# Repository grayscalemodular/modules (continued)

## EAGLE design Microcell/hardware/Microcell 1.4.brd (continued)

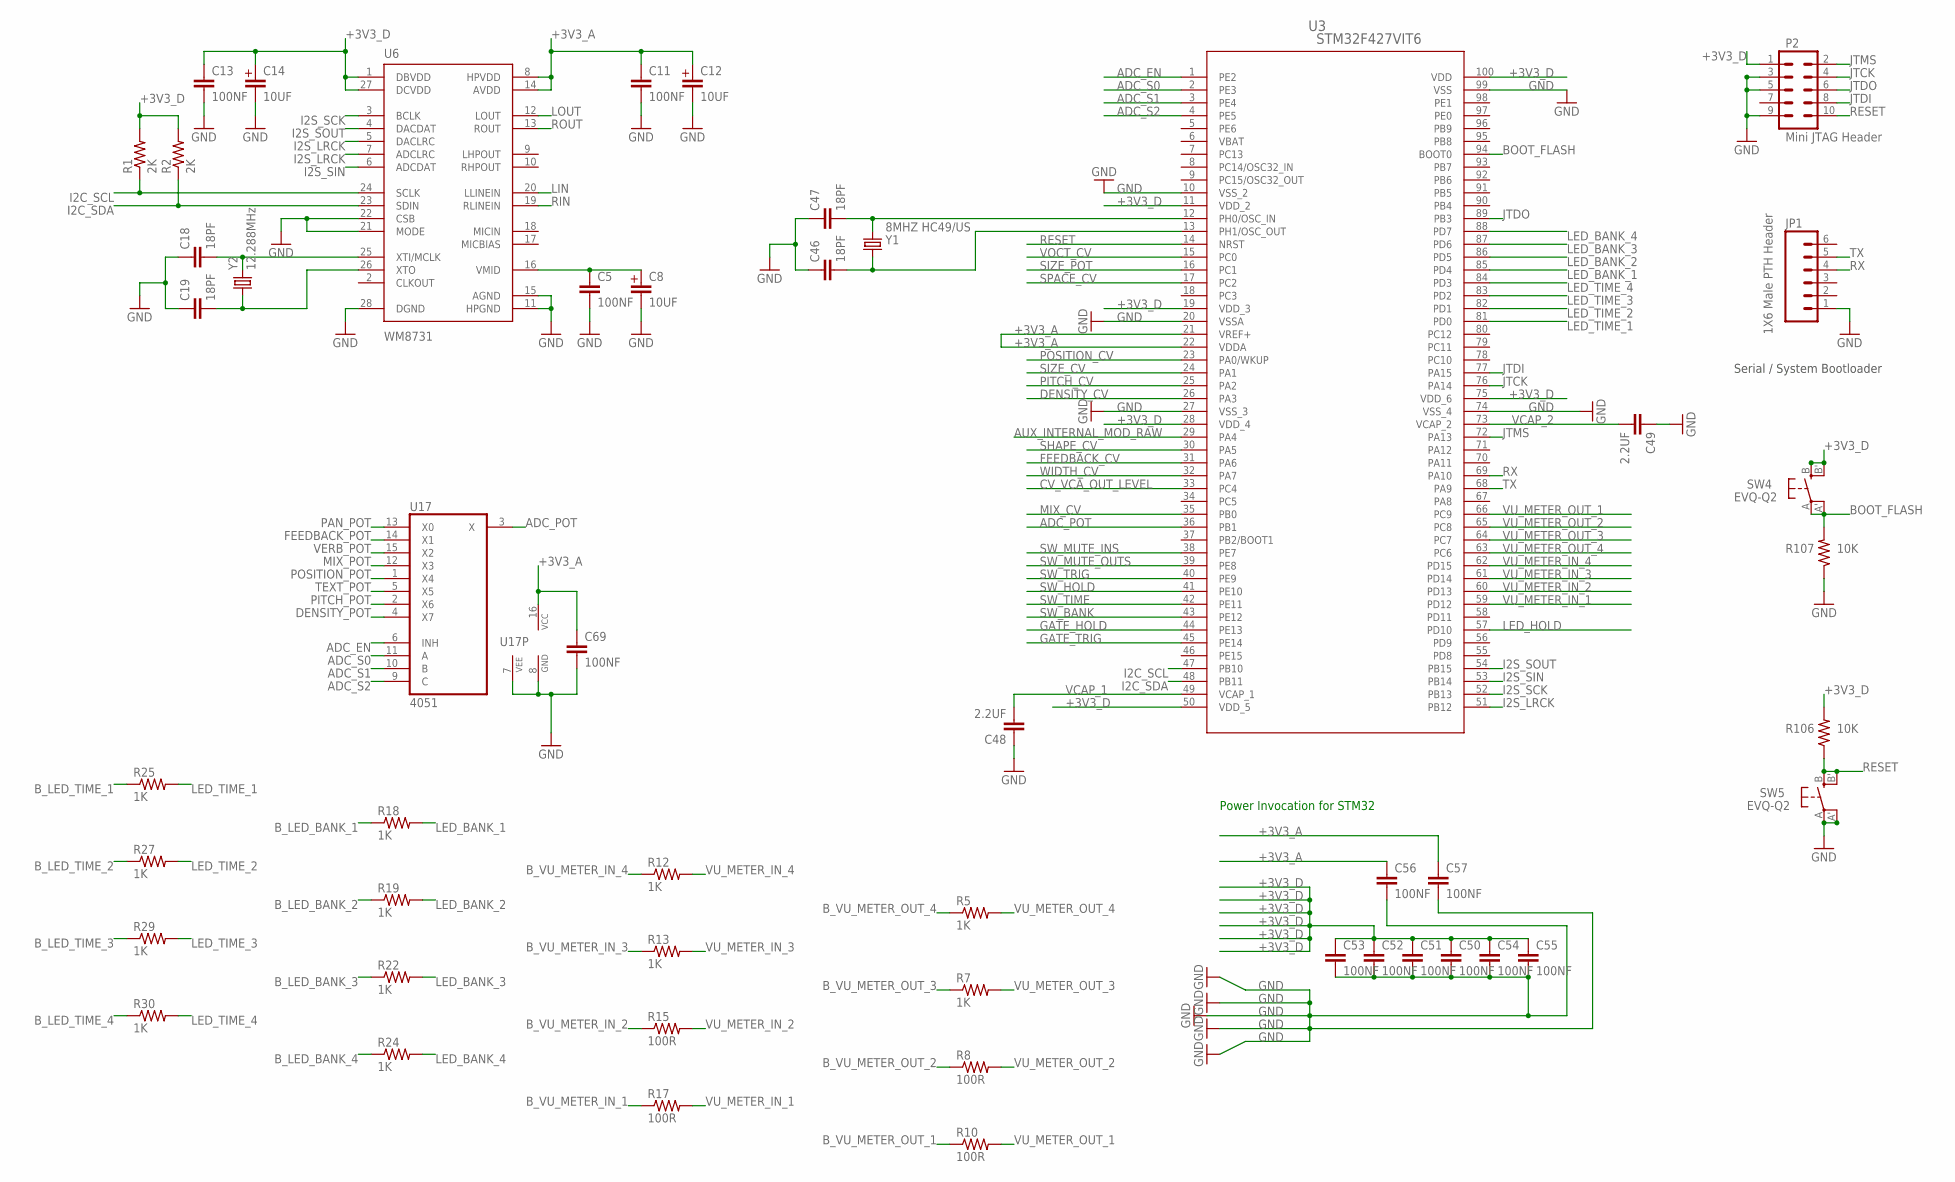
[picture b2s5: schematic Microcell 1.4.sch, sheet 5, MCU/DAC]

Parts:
C5, C11, C13, C50, C51, C52, C53, C54, C55, C56, C57, C69: 100NF; C0603
C8, C12, C14: 10UF; EC-4X7
C18, C19, C46, C47: 18PF; C0603
C48, C49: 2.2UF; C0603
JP1: 1X6 Male PTH Header; 1X06
P2: Mini JTAG Header; 2X5-1.27
R1, R2: 2K; R0603
R5, R7, R12, R13, R18, R19, R22, R24, R25, R27, R29, R30: 1K; R0603
R8, R10, R15, R17: 100R; R0603
R106, R107: 10K; R0603
SW4, SW5: EVQ-Q2
U3: STM32F427VIT6; LQFP100-14X14MM
U6: WM8731; SSOP-28
U17: 4051; SO-16
Y1: 8MHZ HC49/US; HC49UP
Y2: 12.288MHz; HC49UP

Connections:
+3V3_A: C11.1, C12.P$1 (POS), C56.1, C57.1, C69.1, U3.21 (VREF+), U3.22 (VDDA), U6.8 (HPVDD), U6.14 (AVDD), U17.16 (VCC); also elsewhere on the board
+3V3_D: C13.1, C14.P$1 (POS), C50.1, C51.1, C52.1, C53.1, C54.1, C55.1, P2.1, R1.2, R2.2, R106.2, SW4.B (S), SW4.B' (S1), U3.11 (VDD_2), U3.19 (VDD_3), U3.28 (VDD_4), U3.50 (VDD_5), U3.75 (VDD_6), U3.100 (VDD), U6.1 (DBVDD), U6.27 (DCVDD); also elsewhere on the board
ADC_EN: U3.1 (PE2), U17.6 (INH)
ADC_POT: U3.36 (PB1), U17.3 (X)
ADC_S0: U3.2 (PE3), U17.11 (A)
ADC_S1: U3.3 (PE4), U17.10 (B)
ADC_S2: U3.4 (PE5), U17.9 (C)
AUX_INTERNAL_MOD_RAW: U3.29 (PA4); also elsewhere on the board
BOOT_FLASH: R107.2, SW4.A, SW4.A' (P1), U3.94 (BOOT0)
B_LED_BANK_1: R18.1; also elsewhere on the board
B_LED_BANK_2: R19.1; also elsewhere on the board
B_LED_BANK_3: R22.1; also elsewhere on the board
B_LED_BANK_4: R24.1; also elsewhere on the board
B_LED_TIME_1: R25.1; also elsewhere on the board
B_LED_TIME_2: R27.1; also elsewhere on the board
B_LED_TIME_3: R29.1; also elsewhere on the board
B_LED_TIME_4: R30.1; also elsewhere on the board
B_VU_METER_IN_1: R17.1; also elsewhere on the board
B_VU_METER_IN_2: R15.1; also elsewhere on the board
B_VU_METER_IN_3: R13.1; also elsewhere on the board
B_VU_METER_IN_4: R12.1; also elsewhere on the board
B_VU_METER_OUT_1: R10.1; also elsewhere on the board
B_VU_METER_OUT_2: R8.1; also elsewhere on the board
B_VU_METER_OUT_3: R7.1; also elsewhere on the board
B_VU_METER_OUT_4: R5.1; also elsewhere on the board
CV_VCA_OUT_LEVEL: U3.33 (PC4); also elsewhere on the board
DENSITY_CV: U3.26 (PA3); also elsewhere on the board
DENSITY_POT: U17.4 (X7); also elsewhere on the board
FEEDBACK_CV: U3.31 (PA6); also elsewhere on the board
FEEDBACK_POT: U17.14 (X1); also elsewhere on the board
GATE_HOLD: U3.44 (PE13); also elsewhere on the board
GATE_TRIG: U3.45 (PE14); also elsewhere on the board
GND: C5.2, C8.P$2 (NEG), C11.2, C12.P$2 (NEG), C13.2, C14.P$2 (NEG), C18.1, C19.1, C46.1, C47.1, C48.1, C49.1, C50.2, C51.2, C52.2, C53.2, C54.2, C55.2, C56.2, C57.2, C69.2, JP1.1, P2.3, P2.5, P2.9, R107.1, SW5.A, SW5.A' (P1), U3.10 (VSS_2), U3.20 (VSSA), U3.27 (VSS_3), U3.74 (VSS_4), U3.99 (VSS), U6.11 (HPGND), U6.15 (AGND), U6.21 (MODE), U6.22 (CSB), U6.28 (DGND), U17.7 (VEE), U17.8 (GND); also elsewhere on the board
I2C_SCL: R1.1, U3.47 (PB10), U6.24 (SCLK)
I2C_SDA: R2.1, U3.48 (PB11), U6.23 (SDIN)
I2S_LRCK: U3.51 (PB12), U6.5 (DACLRC), U6.7 (ADCLRC)
I2S_SCK: U3.52 (PB13), U6.3 (BCLK)
I2S_SIN: U3.53 (PB14), U6.6 (ADCDAT)
I2S_SOUT: U3.54 (PB15), U6.4 (DACDAT)
JTCK: P2.4, U3.76 (PA14)
JTDI: P2.8, U3.77 (PA15)
JTDO: P2.6, U3.89 (PB3)
JTMS: P2.2, U3.72 (PA13)
LED_BANK_1: R18.2, U3.85 (PD4)
LED_BANK_2: R19.2, U3.86 (PD5)
LED_BANK_3: R22.2, U3.87 (PD6)
LED_BANK_4: R24.2, U3.88 (PD7)
LED_HOLD: U3.57 (PD10); also elsewhere on the board
LED_TIME_1: R25.2, U3.81 (PD0)
LED_TIME_2: R27.2, U3.82 (PD1)
LED_TIME_3: R29.2, U3.83 (PD2)
LED_TIME_4: R30.2, U3.84 (PD3)
LIN: U6.20 (LLINEIN); also elsewhere on the board
LOUT: U6.12 (LOUT); also elsewhere on the board
MIX_CV: U3.35 (PB0); also elsewhere on the board
MIX_POT: U17.12 (X3); also elsewhere on the board
unnamed: C5.1, C8.P$1 (POS), U6.16 (VMID)
unnamed: C19.2, U6.26 (XTO), Y2.1
unnamed: C18.2, U6.25 (XTI/MCLK), Y2.2
unnamed: C46.2, U3.13 (PH1/OSC_OUT), Y1.1
unnamed: C47.2, U3.12 (PH0/OSC_IN), Y1.2
PAN_POT: U17.13 (X0); also elsewhere on the board
PITCH_CV: U3.25 (PA2); also elsewhere on the board
PITCH_POT: U17.2 (X6); also elsewhere on the board
POSITION_CV: U3.23 (PA0/WKUP); also elsewhere on the board
POSITION_POT: U17.1 (X4); also elsewhere on the board
RESET: P2.10, R106.1, SW5.B (S), SW5.B' (S1), U3.14 (NRST)
RIN: U6.19 (RLINEIN); also elsewhere on the board
ROUT: U6.13 (ROUT); also elsewhere on the board
RX: JP1.4, U3.69 (PA10)
SHAPE_CV: U3.30 (PA5); also elsewhere on the board
SIZE_CV: U3.24 (PA1); also elsewhere on the board
SIZE_POT: U3.16 (PC1); also elsewhere on the board
SPACE_CV: U3.17 (PC2); also elsewhere on the board
SW_BANK: U3.43 (PE12); also elsewhere on the board
SW_HOLD: U3.41 (PE10); also elsewhere on the board
SW_MUTE_INS: U3.38 (PE7); also elsewhere on the board
SW_MUTE_OUTS: U3.39 (PE8); also elsewhere on the board
SW_TIME: U3.42 (PE11); also elsewhere on the board
SW_TRIG: U3.40 (PE9); also elsewhere on the board
TEXT_POT: U17.5 (X5); also elsewhere on the board
TX: JP1.5, U3.68 (PA9)
VBAT: U3.6 (VBAT)
VCAP_1: C48.2, U3.49 (VCAP_1)
VCAP_2: C49.2, U3.73 (VCAP_2)
VERB_POT: U17.15 (X2); also elsewhere on the board
VOCT_CV: U3.15 (PC0); also elsewhere on the board
VU_METER_IN_1: R17.2, U3.59 (PD12)
VU_METER_IN_2: R15.2, U3.60 (PD13)
VU_METER_IN_3: R13.2, U3.61 (PD14)
VU_METER_IN_4: R12.2, U3.62 (PD15)
VU_METER_OUT_1: R10.2, U3.66 (PC9)
VU_METER_OUT_2: R8.2, U3.65 (PC8)
VU_METER_OUT_3: R7.2, U3.64 (PC7)
VU_METER_OUT_4: R5.2, U3.63 (PC6)
WIDTH_CV: U3.32 (PA7); also elsewhere on the board

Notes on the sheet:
Power Invocation for STM32
Serial / System Bootloader

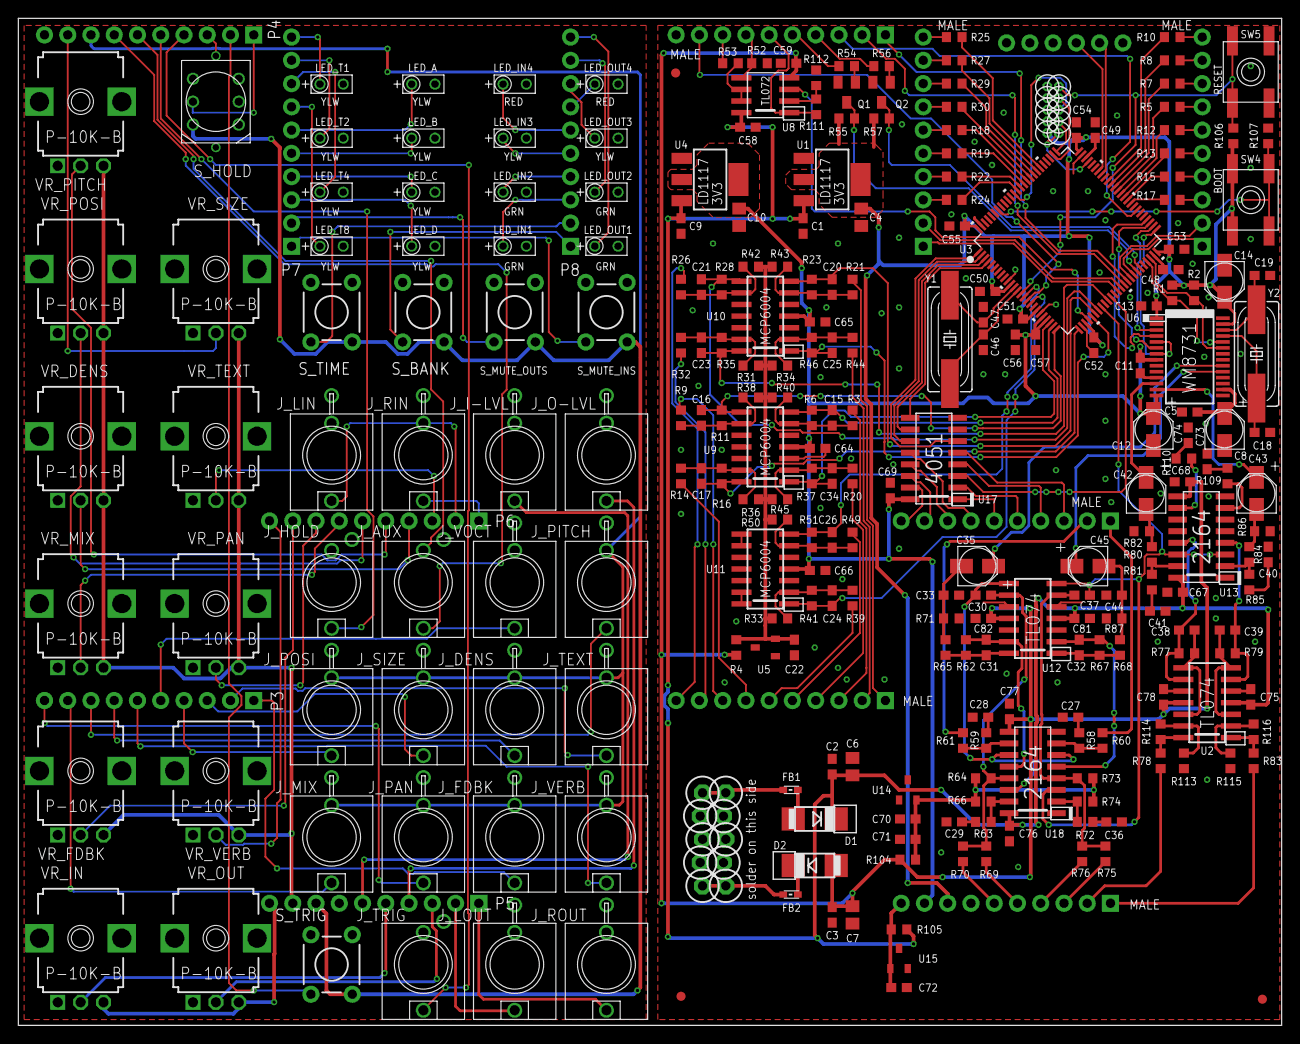
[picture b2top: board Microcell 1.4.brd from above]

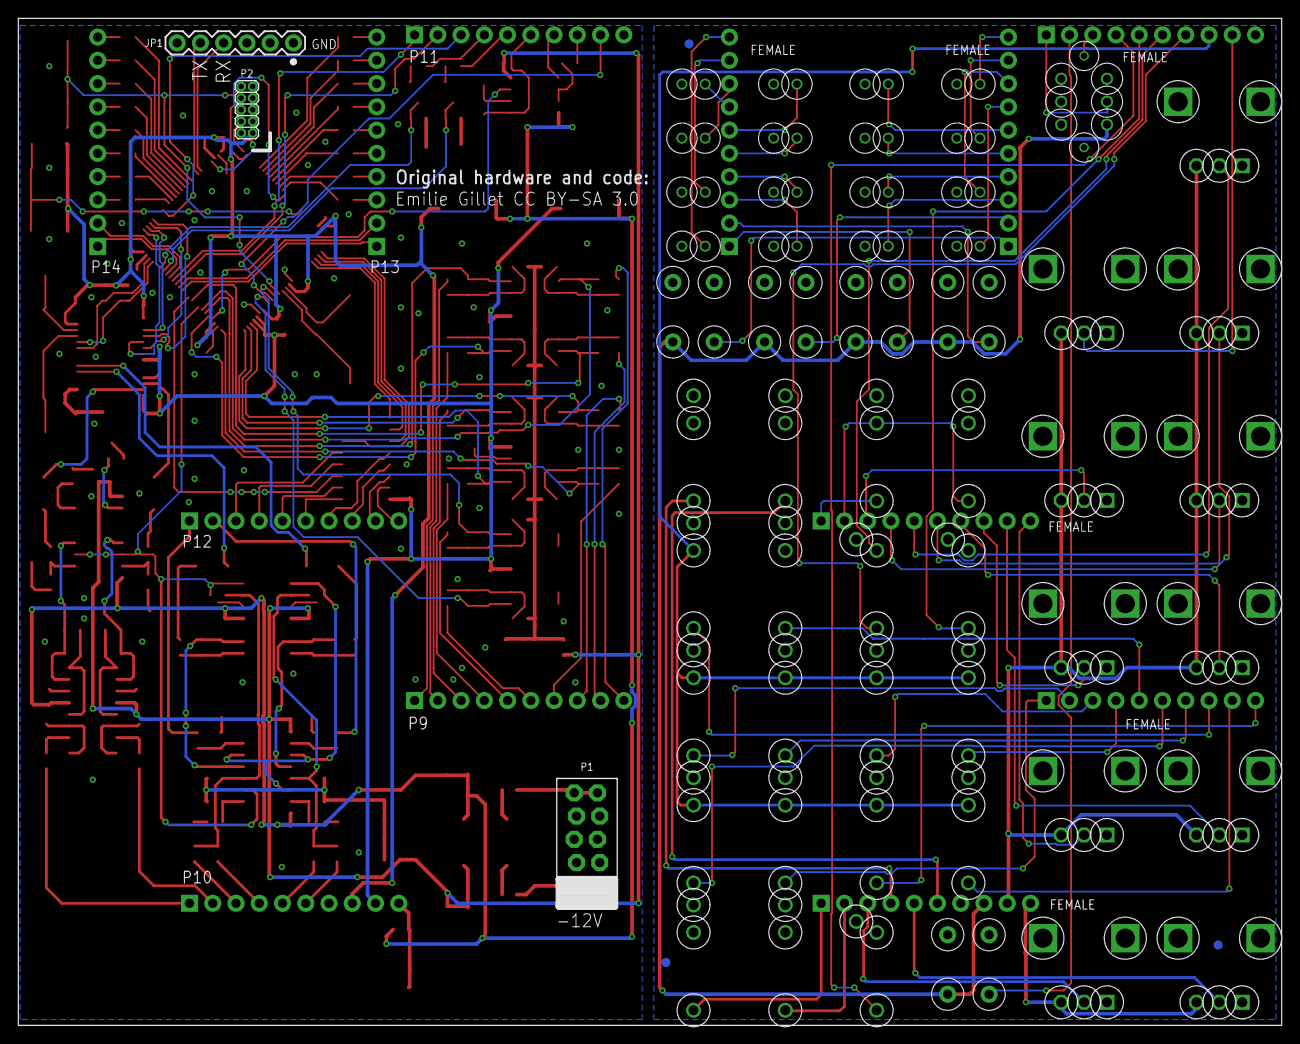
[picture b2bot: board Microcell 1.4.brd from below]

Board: 2 copper layers, 138.0 x 110.0 mm, 272 parts (6 on the bottom side), 237 nets.

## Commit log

2020-08-14 rebuilding repo
